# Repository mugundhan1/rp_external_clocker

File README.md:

# rp_external_clocker
externally clocking stemlab

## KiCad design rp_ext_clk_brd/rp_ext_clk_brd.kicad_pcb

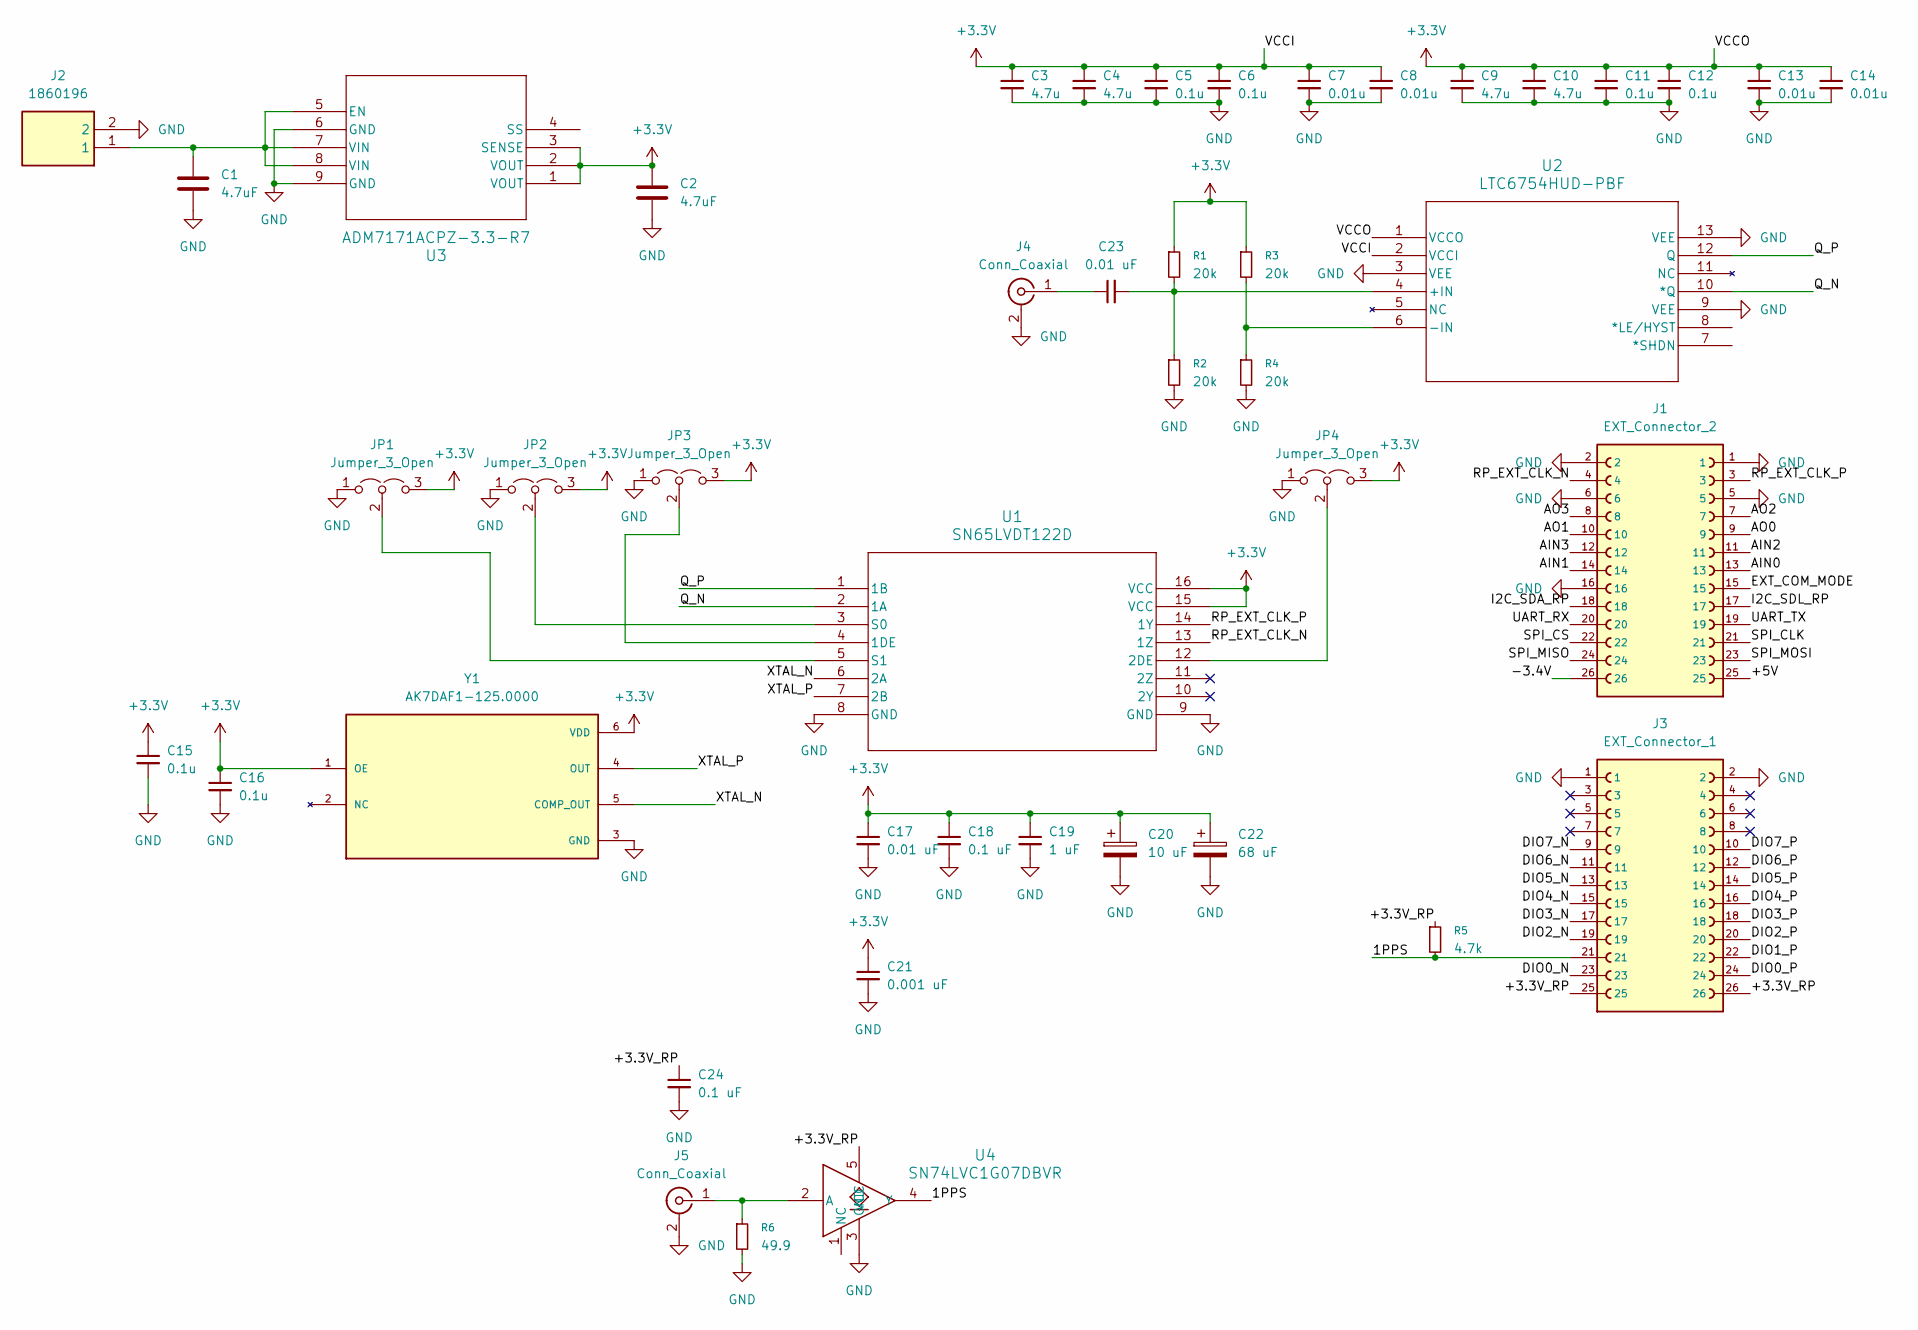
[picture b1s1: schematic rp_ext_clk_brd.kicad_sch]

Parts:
C1, C2: 4.7uF; C_0805_2012Metric
C3, C4, C9, C10: 4.7u; C_1210_3225Metric
C5, C6, C11, C12, C15, C16: 0.1u; C_1210_3225Metric
C7, C8, C13, C14: 0.01u; C_0603_1608Metric
C17, C23: 0.01 uF; C_0603_1608Metric
C18, C24: 0.1 uF; C_1206_3216Metric
C19: 1 uF; C_1206_3216Metric
C20: 10 uF; CAP_TPS_D_AVX
C21: 0.001 uF; C_0603_1608Metric
C22: 68 uF; CAP_593D-D_VSS
J1: EXT_Connector_2; 3M_8526-4500PL; PARTREV April 11, 2008
J2: 1860196; Mouser Part Number 651-1860196
J3: EXT_Connector_1; 3M_8526-4500PL; PARTREV April 11, 2008
J4, J5: Conn_Coaxial; SMA_Samtec_SMA-J-P-H-ST-EM1_EdgeMount
JP1, JP2, JP3, JP4: Jumper_3_Open; PinHeader_1x03_P2.54mm_Vertical
R1, R2, R3, R4: 20k; R_0603_1608Metric
R5: 4.7k; R_0603_1608Metric
R6: 49.9; R_0603_1608Metric
U1: SN65LVDT122D; D16
U2: LTC6754HUD-PBF; QFN12_UD_ADI
U3: ADM7171ACPZ-3.3-R7; CP-8-21_ADI
U4: SN74LVC1G07DBVR; DBV0005A_L
Y1: AK7DAF1-125.0000; XTAL_AK7DAF1-125.0000; PARTREV 04.15.2019

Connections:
+3.3V: C2.1, C3.1, C4.1, C5.1, C6.1, C7.1, C8.1, C9.1, C10.1, C11.1, C12.1, C13.1, C14.1, C15.1, C16.1, C17.1, C18.1, C19.1, C20.1, C21.1, C22.1, JP1.3 (B), JP2.3 (B), JP3.3 (B), JP4.3 (B), R1.1, R3.1, U1.15 (VCC), U1.16 (VCC), U2.1 (VCCO), U2.2 (VCCI), U3.1 (VOUT), U3.2 (VOUT), U3.3 (SENSE), Y1.1 (OE), Y1.6 (VDD)
/1PPS: J3.21, R5.2, U4.4 (Y)
/+3.3V_RP: C24.1, J3.25, J3.26, R5.1, U4.5 (VCC)
/+5V: J1.25
/-3.4V: J1.26
/AIN0: J1.13
/AIN1: J1.14
/AIN2: J1.11
/AIN3: J1.12
/AO0: J1.9
/AO1: J1.10
/AO2: J1.7
/AO3: J1.8
/DIO0_N: J3.23
/DIO0_P: J3.24
/DIO1_P: J3.22
/DIO2_N: J3.19
/DIO2_P: J3.20
/DIO3_N: J3.17
/DIO3_P: J3.18
/DIO4_N: J3.15
/DIO4_P: J3.16
/DIO5_N: J3.13
/DIO5_P: J3.14
/DIO6_N: J3.11
/DIO6_P: J3.12
/DIO7_N: J3.9
/DIO7_P: J3.10
/EXT_COM_MODE: J1.15
/I2C_SDA_RP: J1.18
/I2C_SDL_RP: J1.17
/Q_N: U1.2 (1A), U2.10 (*Q)
/Q_P: U1.1 (1B), U2.12 (Q)
/RP_EXT_CLK_N: J1.4, U1.13 (1Z)
/RP_EXT_CLK_P: J1.3, U1.14 (1Y)
/SPI_CLK: J1.21
/SPI_CS: J1.22
/SPI_MISO: J1.24
/SPI_MOSI: J1.23
/UART_RX: J1.20
/UART_TX: J1.19
/XTAL_N: U1.6 (2A), Y1.5 (COMP_OUT)
/XTAL_P: U1.7 (2B), Y1.4 (OUT)
GND: C1.2, C2.2, C3.2, C4.2, C5.2, C6.2, C7.2, C8.2, C9.2, C10.2, C11.2, C12.2, C13.2, C14.2, C15.2, C16.2, C17.2, C18.2, C19.2, C20.2, C21.2, C22.2, C24.2, J1.1, J1.2, J1.5, J1.6, J1.16, J2.2, J3.1, J3.2, J4.2 (Ext), J5.2 (Ext), JP1.1 (A), JP2.1 (A), JP3.1 (A), JP4.1 (A), R2.2, R4.2, R6.2, U1.8 (GND), U1.9 (GND), U2.3 (VEE), U2.9 (VEE), U2.13 (VEE), U3.6 (GND), U3.9 (GND), U4.3 (GND), Y1.3 (GND)
unnamed: C23.1, J4.1 (In)
unnamed: J5.1 (In), R6.1, U4.2 (A)
unnamed: JP1.2 (C), U1.5 (S1)
unnamed: JP2.2 (C), U1.3 (S0)
unnamed: JP3.2 (C), U1.4 (1DE)
unnamed: JP4.2 (C), U1.12 (2DE)
unnamed: C23.2, R1.2, R2.1, U2.4 (+IN)
unnamed: R3.2, R4.1, U2.6 (-IN)
unnamed: C1.1, J2.1, U3.5 (EN), U3.7 (VIN), U3.8 (VIN)

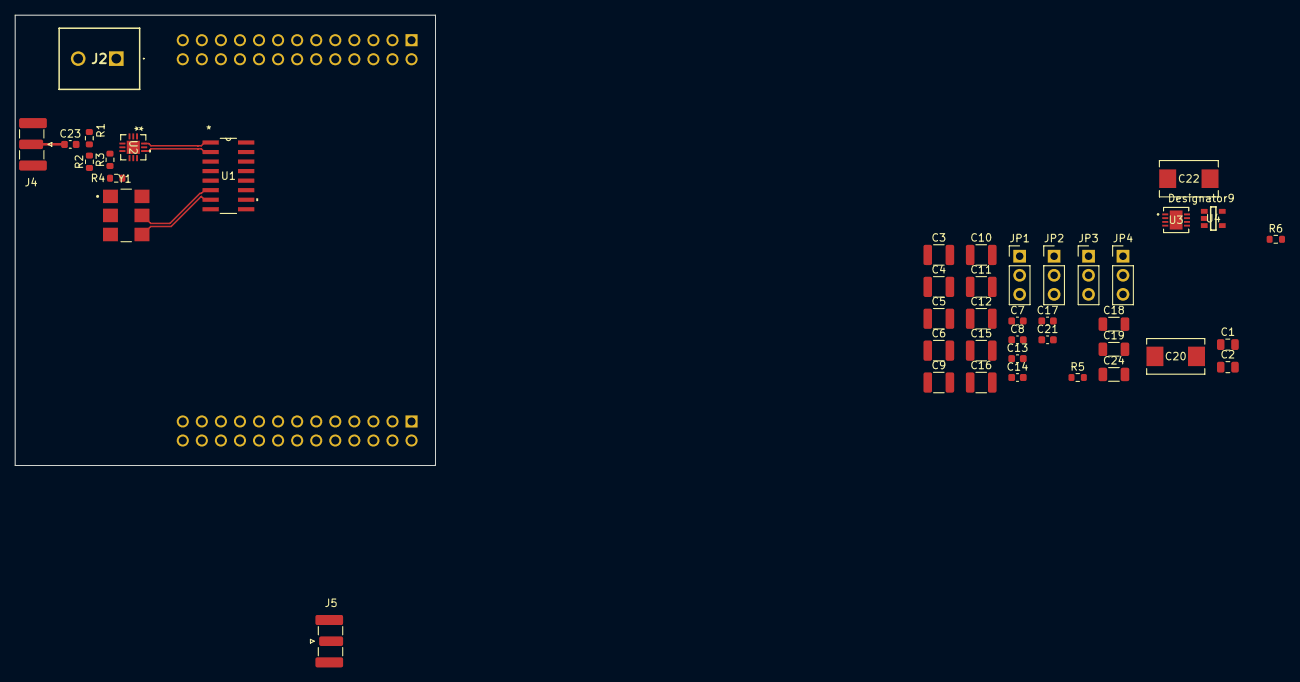
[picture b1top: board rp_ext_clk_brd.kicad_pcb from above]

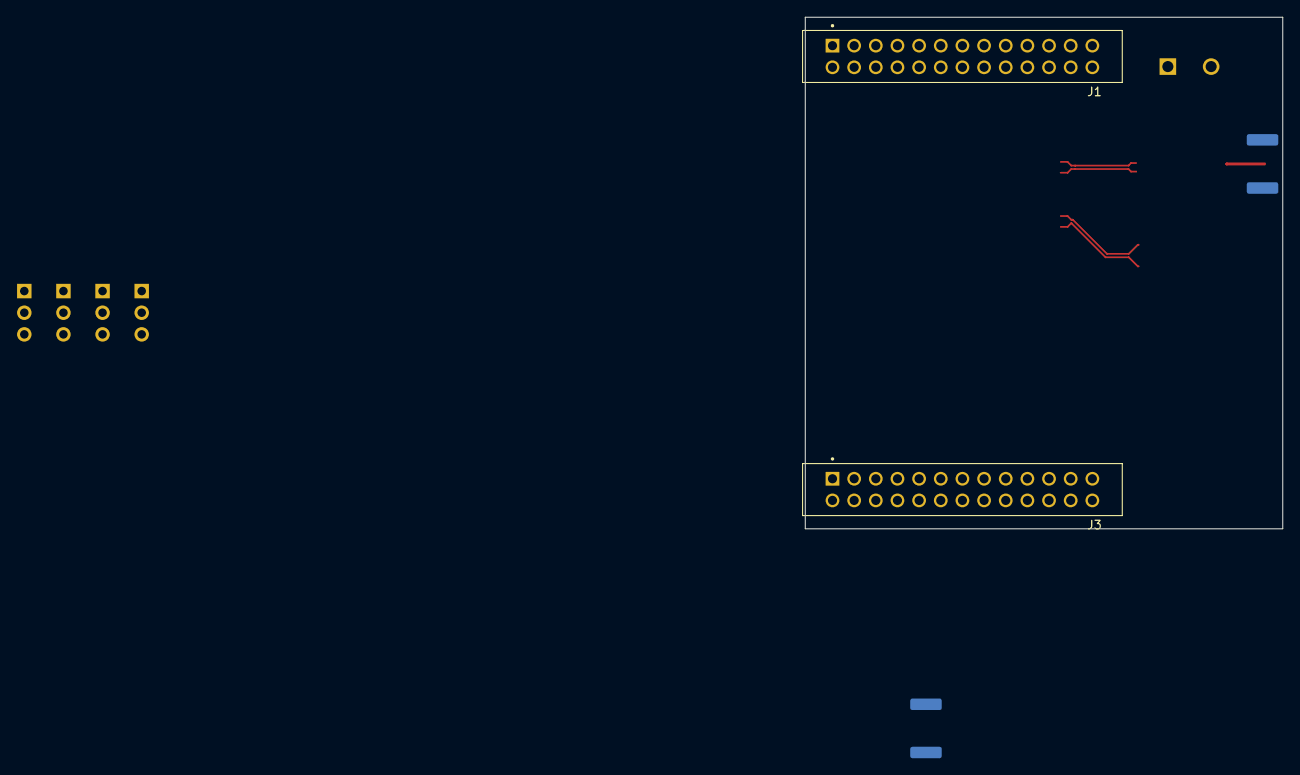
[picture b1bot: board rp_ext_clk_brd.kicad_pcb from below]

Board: 4 copper layers, 56.0 x 60.0 mm, 44 parts (2 on the bottom side), 19 nets.

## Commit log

2026-02-28 first
2026-03-02 adding decoupling and power supply
2026-03-05 further changes
2026-03-05 schematic almost done
2026-03-05 assigned bom for capacitors
2026-03-06 netlist compiled, exported to pcb
2026-03-06 started routing
